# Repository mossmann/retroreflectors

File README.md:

retroreflectors
===============

RF retroreflectors

## CONGAFLOCK
A general purpose FET based RF retroreflector

## FLAMENCOFLOCK
A retroreflector for PS/2 keyboard monitoring (unfinished)

## RUMBAFLOCK
A general purpose PIN diode based RF retroreflector

## SALSAFLOCK
A retroreflector for VGA monitoring (unfinished)

## TANGOFLOCK
A retroreflector for USB keyboard monitoring

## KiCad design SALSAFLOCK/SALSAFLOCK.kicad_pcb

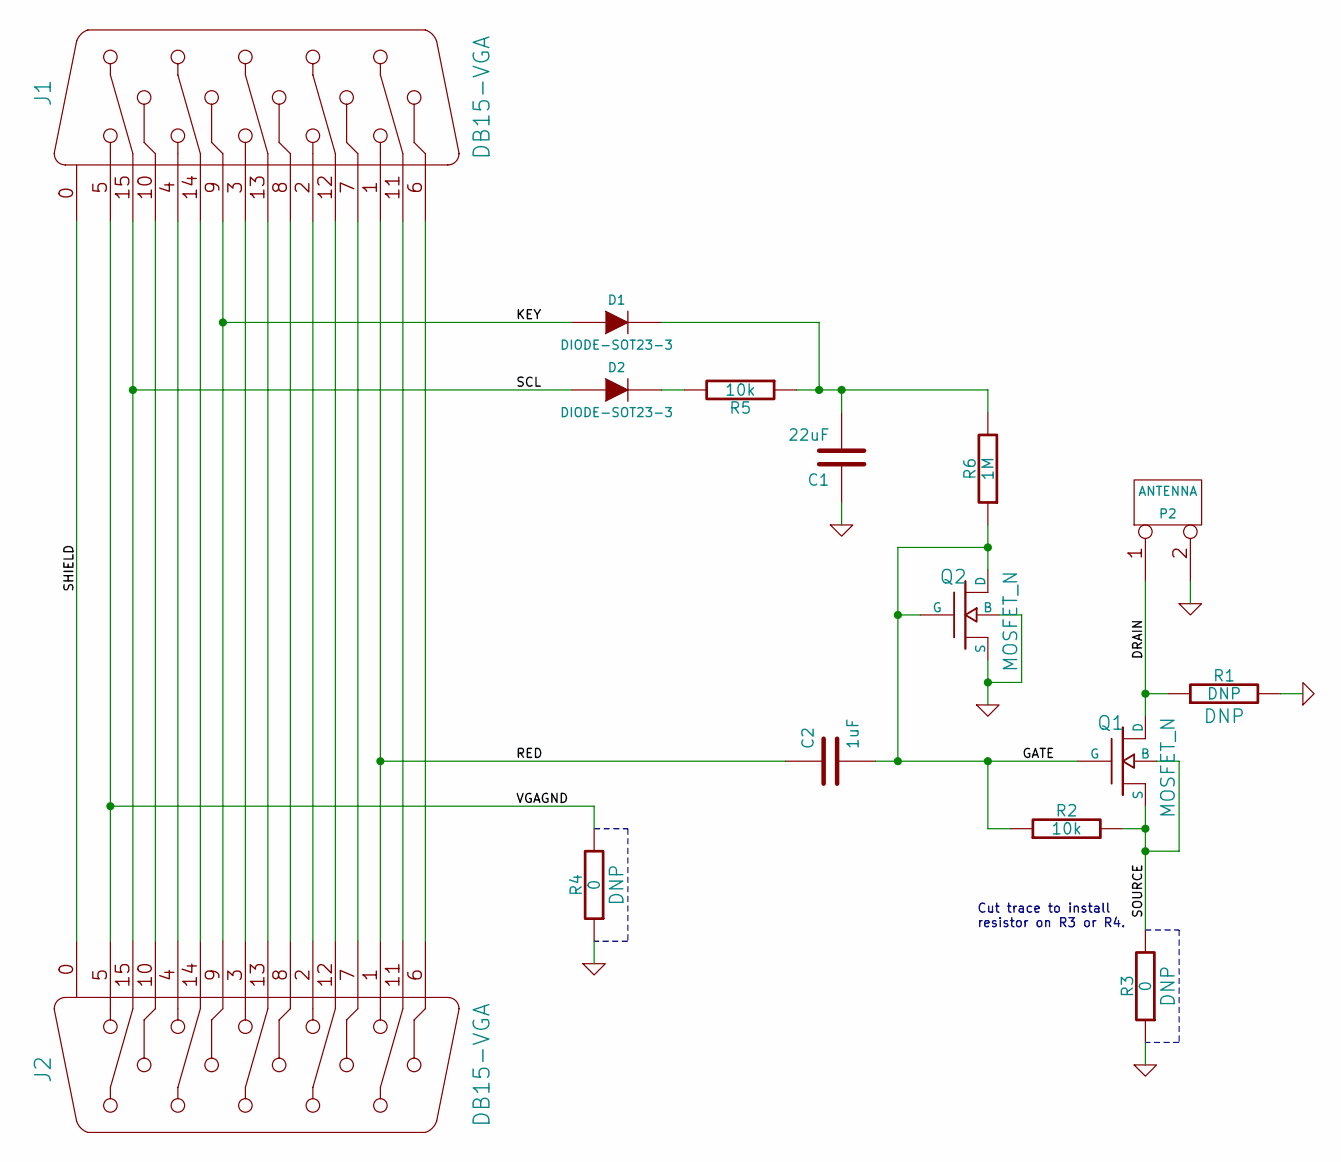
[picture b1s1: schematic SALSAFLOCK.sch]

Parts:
C1: 22uF
C2: 1uF
D1, D2: DIODE-SOT23-3; Part Number BAT54
J1, J2: DB15-VGA
P2: ANTENNA
Q1, Q2: MOSFET_N; Part Number BSS83,215
R1: DNP
R2, R5: 10k
R3, R4: 0
R6: 1M

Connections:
/DRAIN: P2.1, Q1.D, R1.1
/GATE: C2.2, Q1.G, Q2.D, Q2.G, R2.1, R6.1
/KEY: D1.1 (A), J1.9, J2.9
/RED: C2.1, J1.1, J2.1
/SCL: D2.1 (A), J1.15, J2.15
/SHIELD: J1.0 (SHIELD), J2.0 (SHIELD)
/SOURCE: Q1.B, Q1.S, R2.2, R3.2
/VGAGND: J1.5, J2.5, R4.2
GND: C1.1, P2.2 (PM), Q2.B, Q2.S, R1.2, R3.1, R4.1
unnamed: J1.10, J2.10
unnamed: J1.7, J2.7
unnamed: J1.2, J2.2
unnamed: J1.3, J2.3
unnamed: J1.4, J2.4
unnamed: J1.6, J2.6
unnamed: J1.8, J2.8
unnamed: J1.11 (P111), J2.11 (P111)
unnamed: J1.12, J2.12
unnamed: J1.13, J2.13
unnamed: J1.14, J2.14
unnamed: D2.3 (K), R5.2
unnamed: C1.2, D1.3 (K), R5.1, R6.2

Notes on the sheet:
Cut trace to install resistor on R3 or R4.

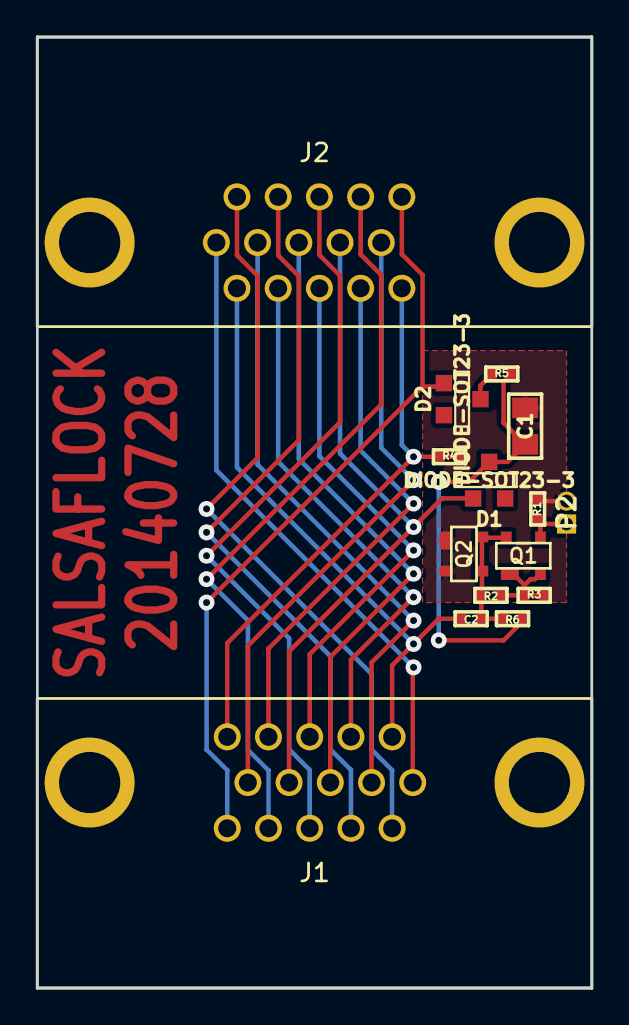
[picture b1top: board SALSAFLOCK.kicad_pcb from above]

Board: 2 copper layers, 30.8 x 52.8 mm, 15 parts (0 on the bottom side), 22 nets.

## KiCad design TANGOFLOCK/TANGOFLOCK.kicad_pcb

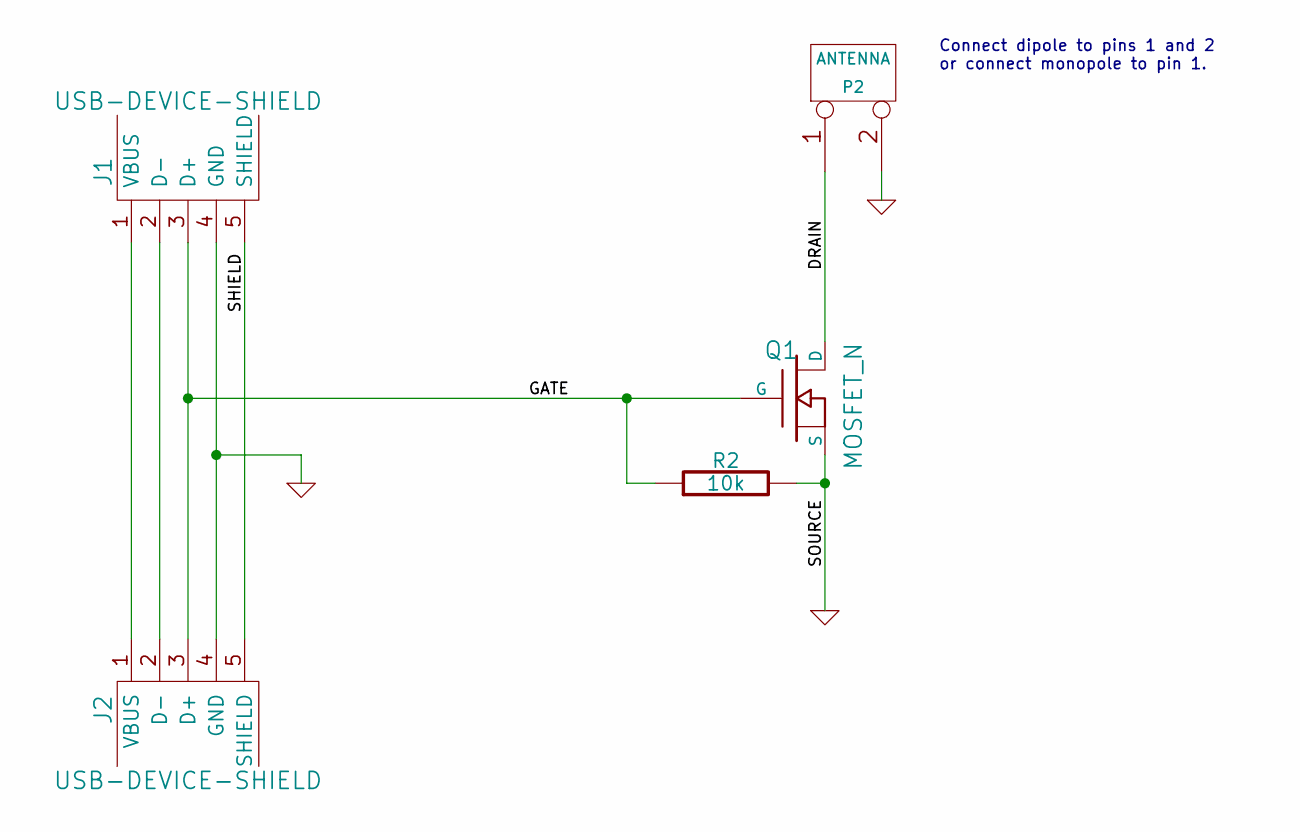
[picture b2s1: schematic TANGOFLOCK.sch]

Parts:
J1, J2: USB-DEVICE-SHIELD
P2: ANTENNA
Q1: MOSFET_N; Part Number BSS83,215
R2: 10k

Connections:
/DRAIN: P2.1, Q1.D
/GATE: J1.3 (D+), J2.3 (D+), Q1.G, R2.1
/SHIELD: J1.5 (SHIELD), J2.5 (SHIELD)
GND: J1.4 (GND), J2.4 (GND), P2.2 (PM), Q1.S, R2.2
unnamed: J1.2 (D-), J2.2 (D-)
unnamed: J1.1 (VBUS), J2.1 (VBUS)

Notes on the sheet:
Connect dipole to pins 1 and 2 or connect monopole to pin 1.

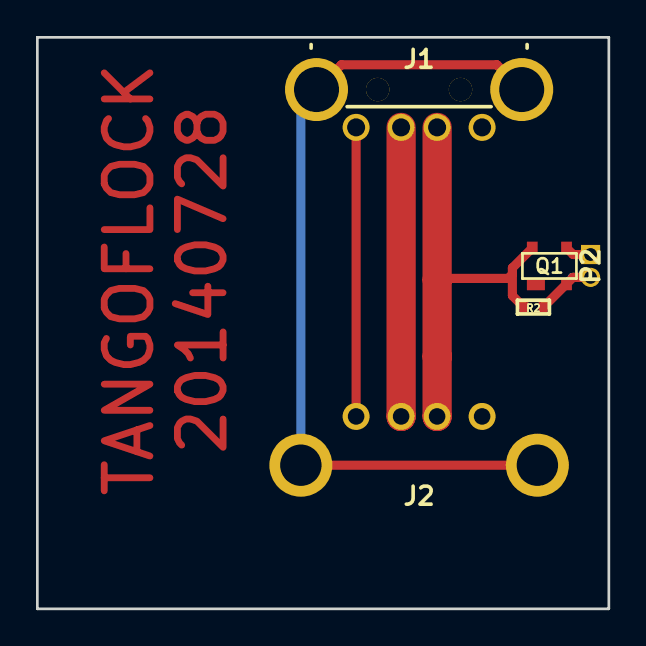
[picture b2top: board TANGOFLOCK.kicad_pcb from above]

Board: 2 copper layers, 31.8 x 31.8 mm, 5 parts (0 on the bottom side), 6 nets.

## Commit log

2014-07-16 CONGAFLOCK: a general purpose FET based RF retroreflector
2014-07-16 RUMBAFLOCK: a general purpose PIN diode based RF retroreflector
2014-07-16 SALSAFLOCK: a retroreflector for VGA monitoring (unfinished)
2014-07-16 URL on schematic
2014-07-17 added VGA connectors
2014-07-17 connector layout
2014-07-23 selected a new MOSFET
2014-07-28 finished SALSAFLOCK
2014-07-28 improved via annular ring
2014-07-28 updated date mark
2014-07-28 FLAMENCOFLOCK: a retroreflector for PS/2 keyboard monitoring (unfinished)
2014-07-29 TANGOFLOCK: a retroreflector for USB keyboard monitoring
2014-07-29 moved text to copper layer
2014-07-29 finished FLAMENCOFLOCK
2014-07-29 simplified TANGOFLOCK
2014-08-13 corrected PS/2 connector footprint (previous workaround was to mount on reverse side)
2014-08-13 connected BSS83,215 substrate to source (previous workaround was solder blob)
2014-08-13 changed R6 to 10k
2015-07-07 added GNU Radio Companion examples for PS2 and VGA
2016-07-12 Add descriptions to readme for ease of finding things

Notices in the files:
TANGOFLOCK/TANGOFLOCK.sch:
Copyright 2014 Michael Ossmann
License: GPL v2, https://github.com/mossmann/retroreflectors
